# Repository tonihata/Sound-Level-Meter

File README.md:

# Sound-Level-Meter

Sound level meter made with own pcb. I used kicad to make the pcb and to manufacture it i used milling. For the software i used Arduino IDE. The case was made using the Autodesk Inventor.

I used the ATMEGA328P -microchip and the MAX4466 -microphone.

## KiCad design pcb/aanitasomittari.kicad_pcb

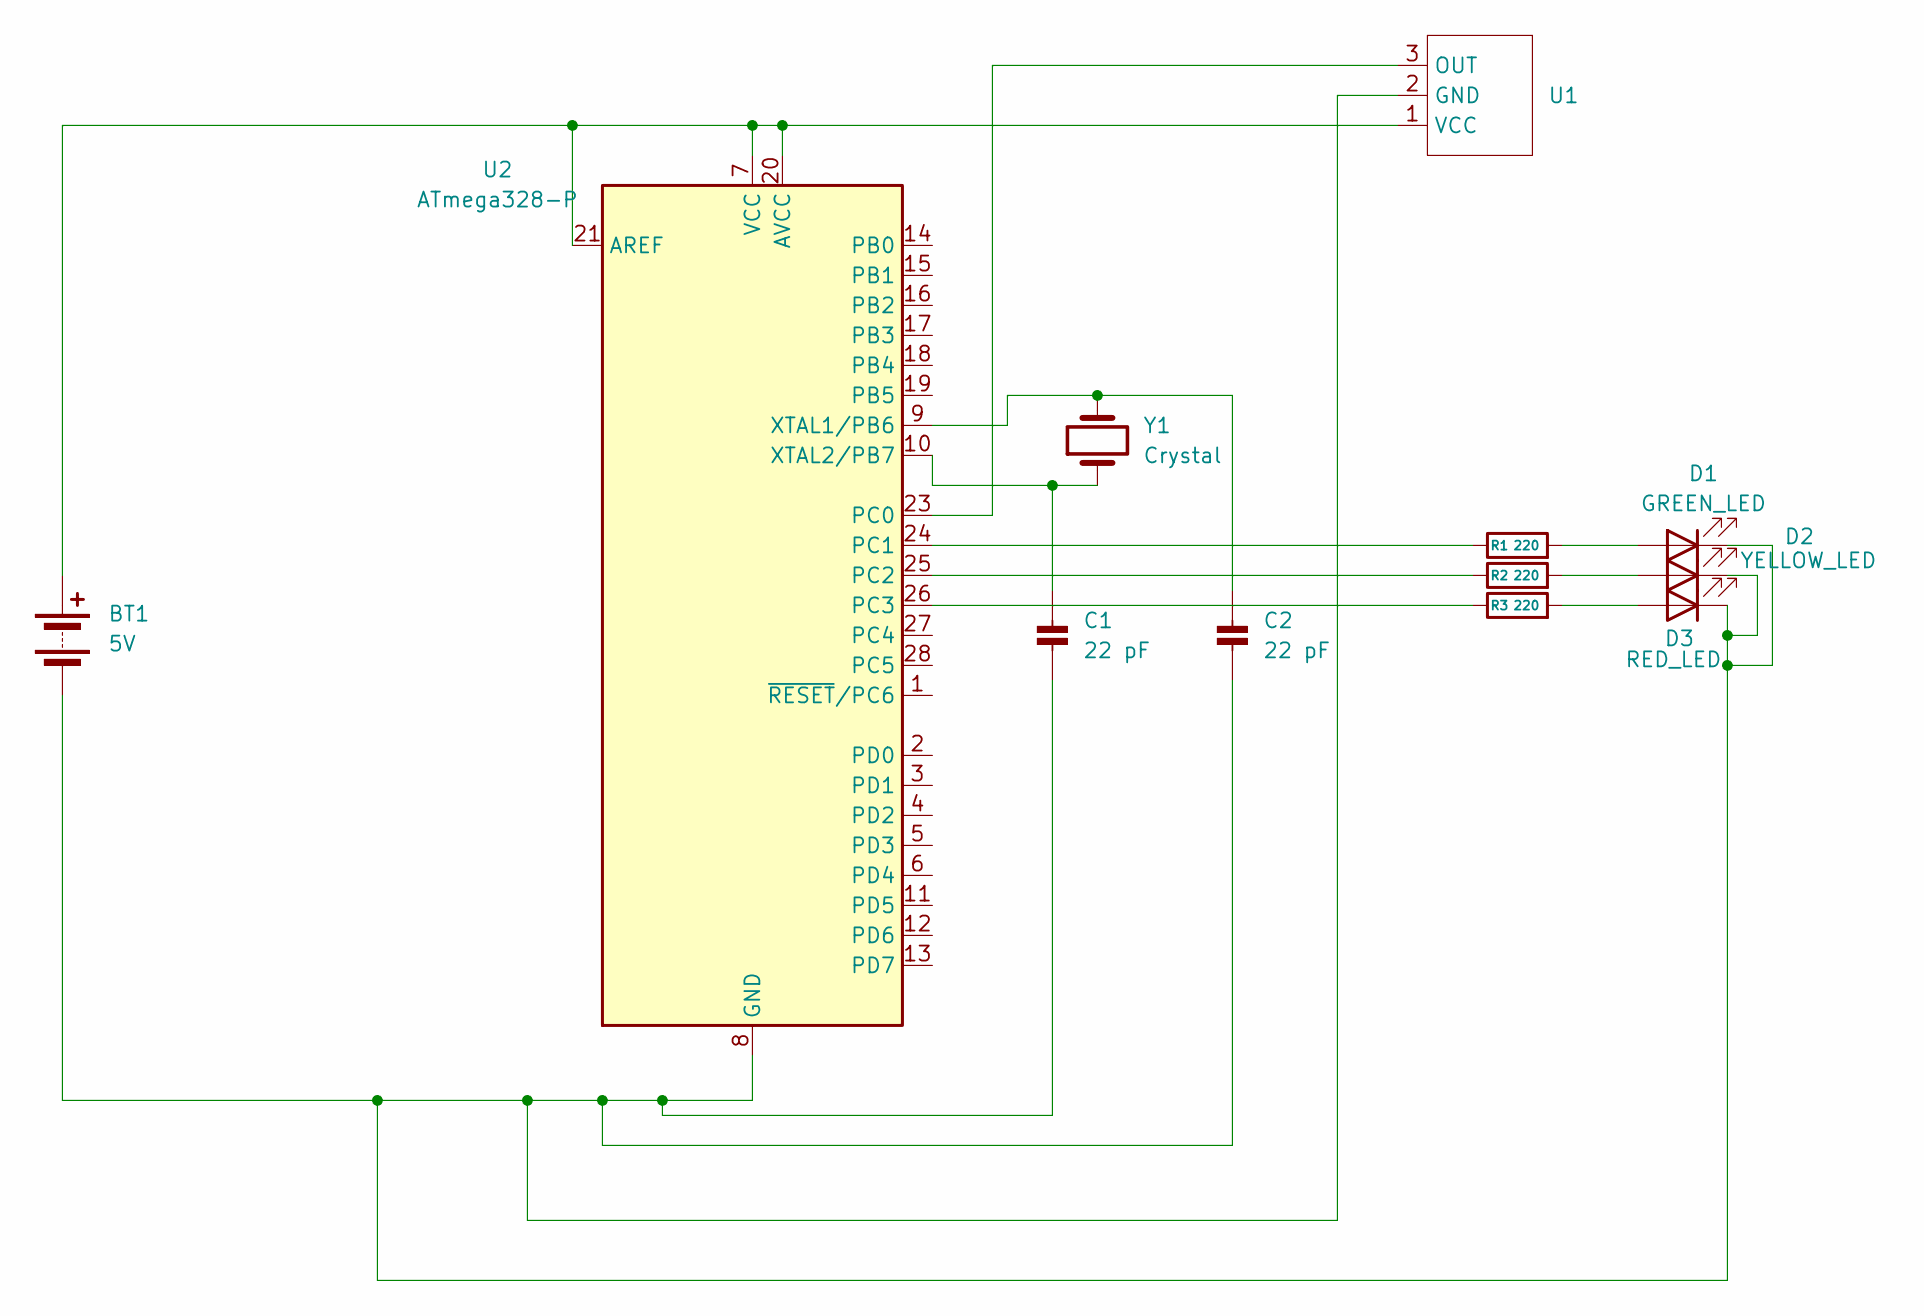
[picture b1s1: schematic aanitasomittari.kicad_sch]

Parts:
BT1: 5V; TerminalBlock_MaiXu_MX126-5.0-02P_1x02_P5.00mm
C1, C2: 22 pF; C_Disc_D8.0mm_W2.5mm_P5.00mm
D1: GREEN_LED; LED_D5.0mm
D2: YELLOW_LED; LED_D5.0mm
D3: RED_LED; LED_D5.0mm
R1, R2, R3: 220; R_Axial_DIN0207_L6.3mm_D2.5mm_P10.16mm_Horizontal
U1: max4466
U2: ATmega328-P; DIP-28_W7.62mm
Y1: Crystal; Crystal_HC49-4H_Vertical

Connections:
unnamed: BT1.1 (+), U1.1 (VCC), U2.7 (VCC), U2.20 (AVCC), U2.21 (AREF)
unnamed: BT1.2 (-), C1.2, C2.2, D1.1 (K), D2.1 (K), D3.1 (K), U1.2 (GND), U2.8 (GND), U2.22 (GND)
unnamed: C1.1, U2.10 (XTAL2/PB7), Y1.1
unnamed: C2.1, U2.9 (XTAL1/PB6), Y1.2
unnamed: D1.2 (A), R1.2
unnamed: D2.2 (A), R2.2
unnamed: D3.2 (A), R3.2
unnamed: U1.3 (OUT), U2.23 (PC0)
unnamed: R1.1, U2.24 (PC1)
unnamed: R2.1, U2.25 (PC2)
unnamed: R3.1, U2.26 (PC3)

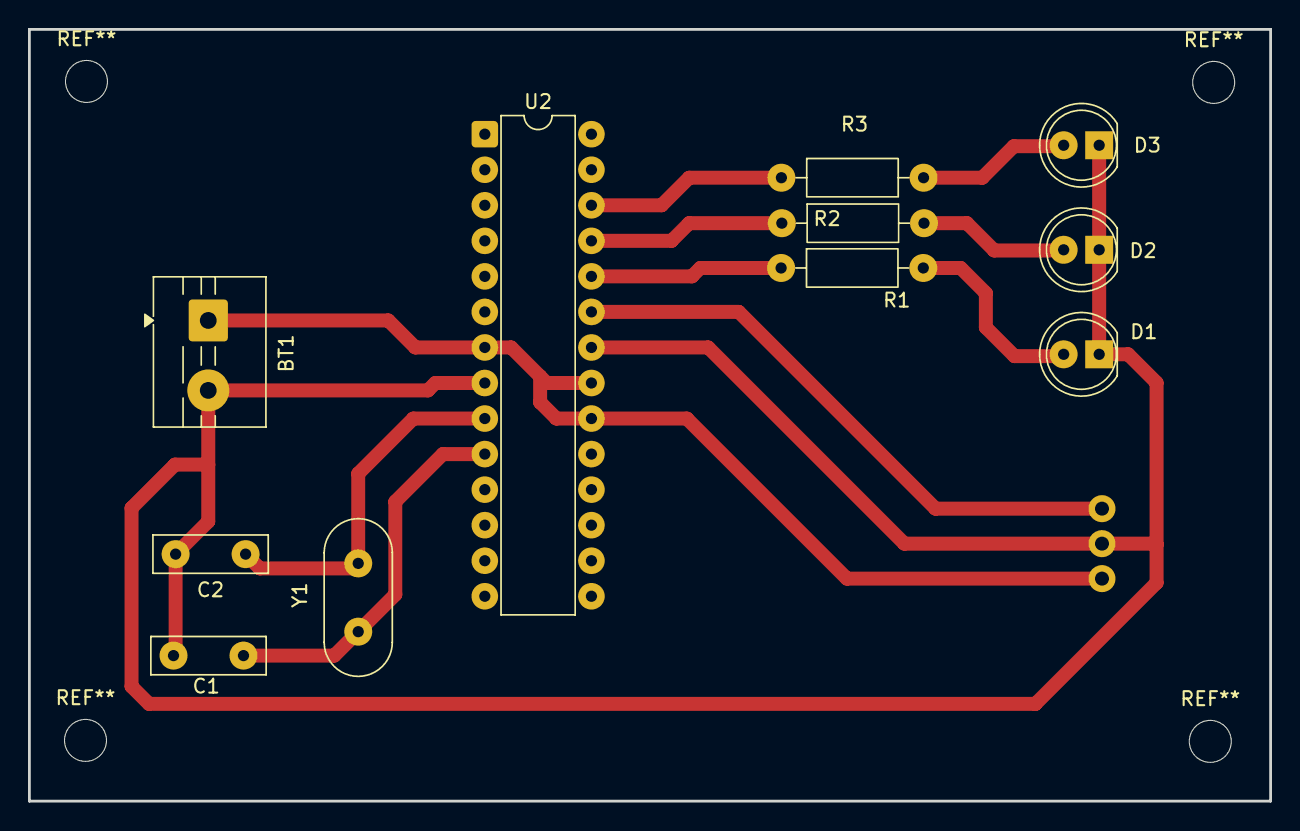
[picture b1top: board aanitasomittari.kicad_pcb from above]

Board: 2 copper layers, 88.7 x 55.1 mm, 12 parts (1 on the bottom side), 11 nets.
